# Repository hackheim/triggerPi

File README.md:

# triggerPi
DSLR Remote trigger kippah  for Raspberry Pi

<br />This work is licensed under a <a rel="license" href="http://creativecommons.org/licenses/by-sa/4.0/">Creative Commons Attribution-ShareAlike 4.0 International License</a>.

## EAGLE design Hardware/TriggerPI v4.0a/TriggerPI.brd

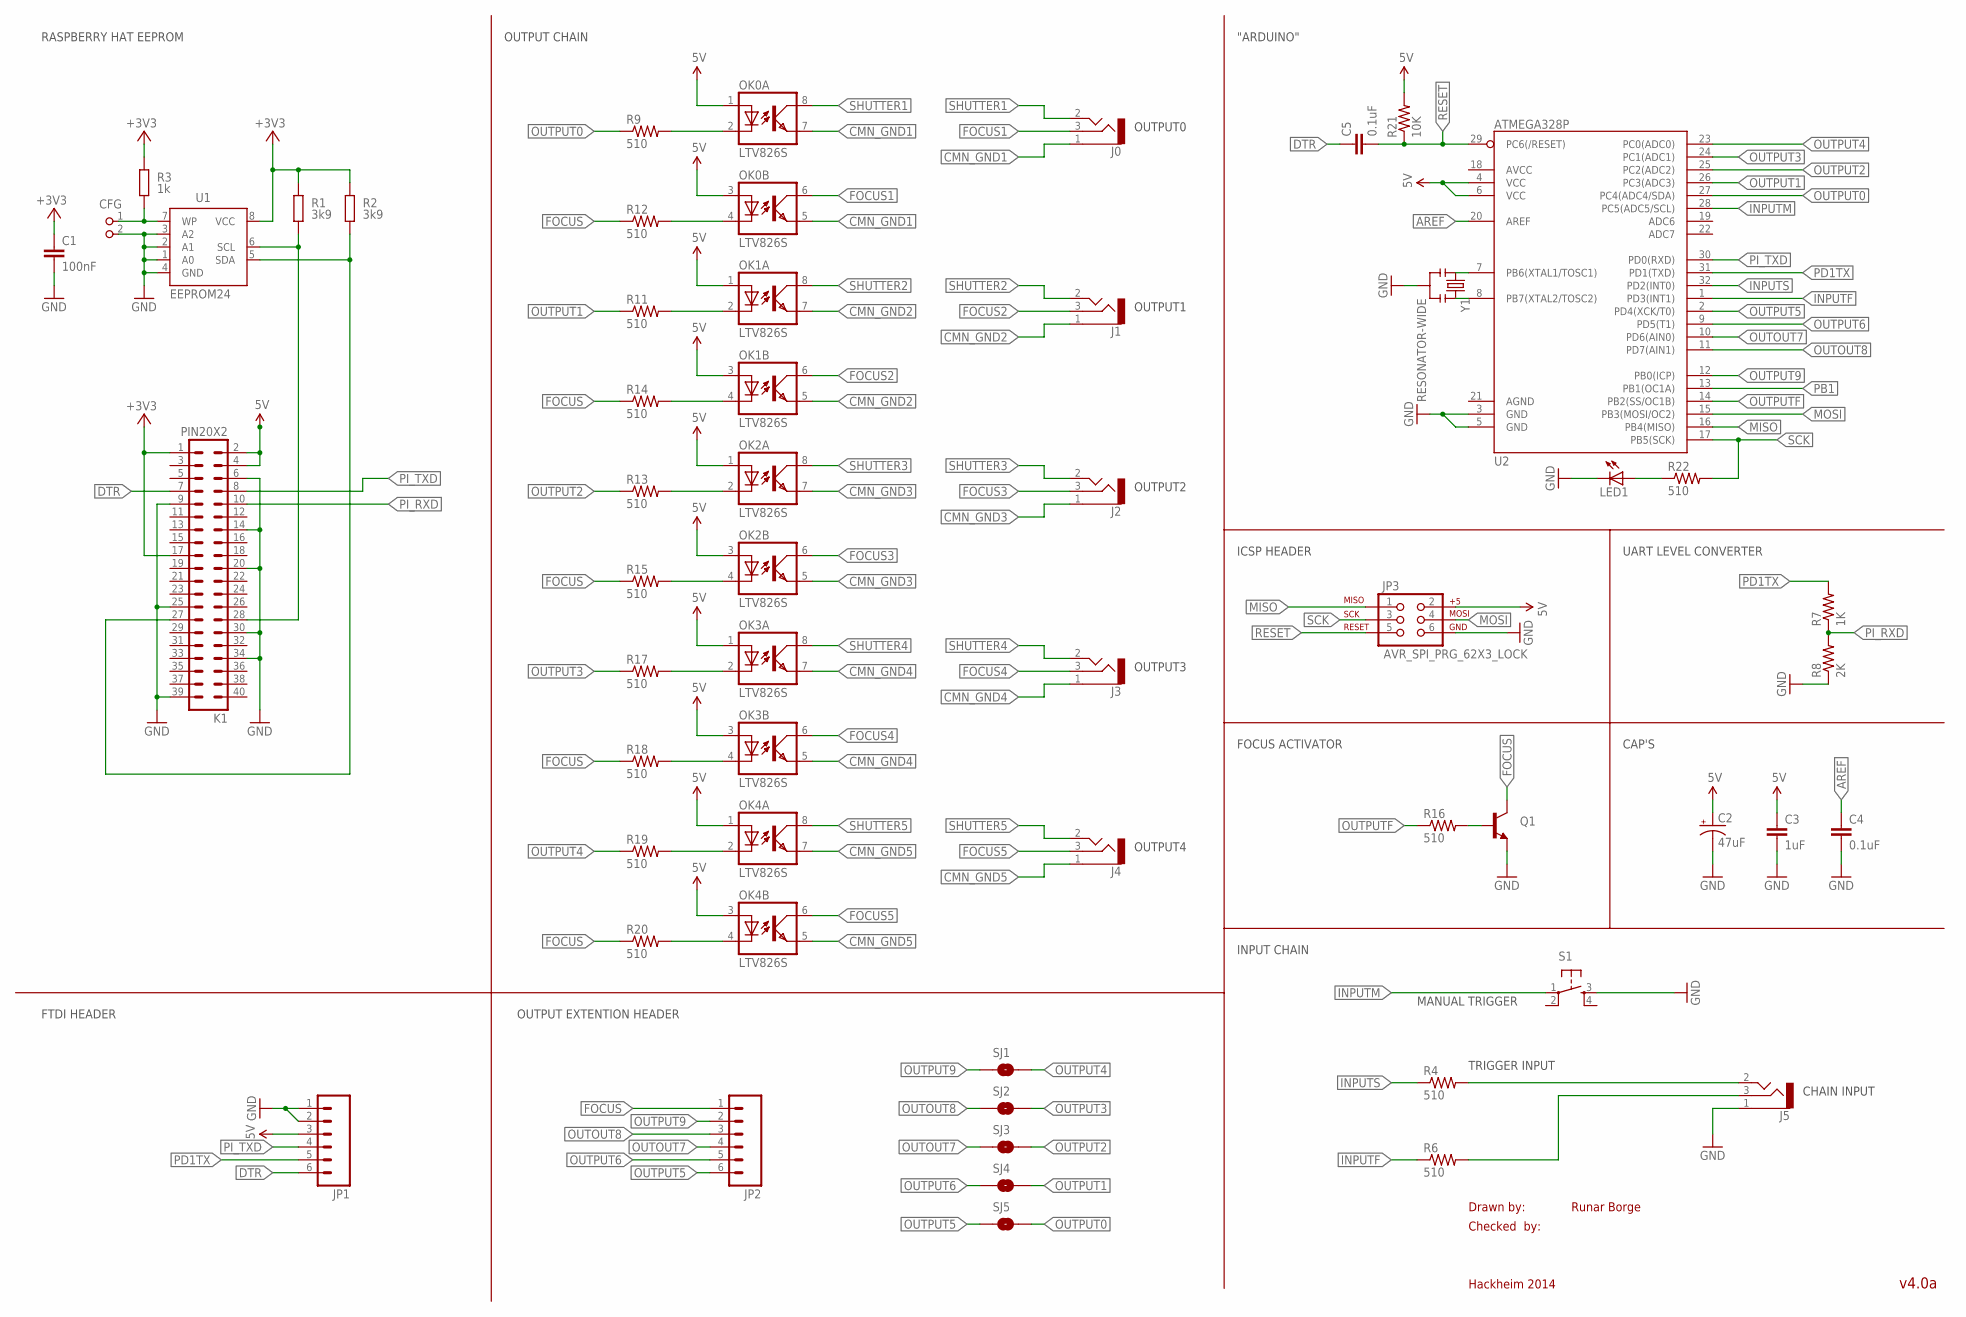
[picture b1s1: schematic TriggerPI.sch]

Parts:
C1: 100nF; C0805K
C2: 47uF; EIA3528; DIGIKEY 478-3132-1-ND
C3: 1uF; 0805; DIGIKEY 445-7547-1-ND
C4, C5: 0.1uF; 0603-CAP; DIGIKEY 445-1314-1-ND
CFG: PIN2_100; PIN_W_2
J0, J1, J2, J3, J4, J5: AUDIO-3P'SJ-3523-SMT'; 3P-SMD-3.5; DIGIKEY CP-3523SJCT-ND
JP1, JP2: M06LOCK; 1X06_LOCK
JP3: AVR_SPI_PRG_62X3_LOCK; 2X3_LOCK
K1: PIN20X2; PIN_20X2
LED1: LED1206; LED-1206; DIGIKEY 160-1405-1-ND
OK0, OK1, OK2, OK3, OK4: LTV826S; DIL8-SMD; DIGIKEY 160-1363-5-ND
Q1: TRANSISTOR_NPNSOT23-3; SOT23-3; DIGIKEY MMBT2222A-FDICT-ND
R1, R2: 3k9; M0805; TOLERANCE 5%
R3: 1k; M0805; TOLERANCE 5%
R4, R6, R9, R11, R12, R13, R14, R15, R16, R17, R18, R19, R20, R22: 510; 0603-RES; DIGIKEY RMCF0603JT510RCT-ND
R7: 1K; 0603-RES; DIGIKEY RMCF0603JT1K00CT-ND
R8: 2K; 0603-RES; DIGIKEY RMCF0603JT2K00CT-ND
R21: 10K; 0603-RES; DIGIKEY RMCF0603JT10K0CT-ND
S1: TAC_SWITCHSMD; TACTILE_SWITCH_SMD; DIGIKEY CKN9104CT-ND
SJ1, SJ2, SJ3, SJ4, SJ5: JUMPER-PAD-2-NOYES_SILK; PAD-JUMPER-2-NO_YES_SILK
U1: EEPROM24; SOIC8
U2: ATMEGA328P; TQFP32-08; DIGIKEY ATMEGA328P-AURCT-ND
Y1: RESONATOR-WIDE; RESONATOR-WIDE-SMD; DIGIKEY 1253-1084-1-ND

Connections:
5V: C2.A (+), C3.1, JP1.3, JP3.2, K1.2, K1.4, OK0.1 (A), OK0.3 (A), OK1.1 (A), OK1.3 (A), OK2.1 (A), OK2.3 (A), OK3.1 (A), OK3.3 (A), OK4.1 (A), OK4.3 (A), R21.2, U2.4 (VCC), U2.6 (VCC)
+3V3: C1.1, K1.1, K1.17, R1.2, R2.2, R3.2, U1.8 (VCC)
AREF: C4.1, U2.20 (AREF)
CMN_GND1: J0.1, OK0.5 (EMIT), OK0.7 (EMIT)
CMN_GND2: J1.1, OK1.5 (EMIT), OK1.7 (EMIT)
CMN_GND3: J2.1, OK2.5 (EMIT), OK2.7 (EMIT)
CMN_GND4: J3.1, OK3.5 (EMIT), OK3.7 (EMIT)
CMN_GND5: J4.1, OK4.5 (EMIT), OK4.7 (EMIT)
DTR: C5.1, JP1.6, K1.7
FOCUS: JP2.1, Q1.3 (C), R12.1, R14.1, R15.1, R18.1, R20.1
FOCUS0: J5.3 (2), R6.2
FOCUS1: J0.3 (2), OK0.6 (COL)
FOCUS2: J1.3 (2), OK1.6 (COL)
FOCUS3: J2.3 (2), OK2.6 (COL)
FOCUS4: J3.3 (2), OK3.6 (COL)
FOCUS5: J4.3 (2), OK4.6 (COL)
GND: C1.2, C2.C (-), C3.2, C4.2, CFG.2, J5.1, JP1.1, JP1.2, JP3.6, K1.6, K1.9, K1.14, K1.20, K1.25, K1.30, K1.34, K1.39, LED1.C, Q1.2 (E), R8.1, S1.3, U1.1 (A0), U1.2 (A1), U1.3 (A2), U1.4 (GND), U2.3 (GND), U2.5 (GND), Y1.2
INPUTF: R6.1, U2.1 (PD3(INT1))
INPUTM: S1.1, U2.28 (PC5(ADC5/SCL))
INPUTS: R4.1, U2.32 (PD2(INT0))
MISO: JP3.1, U2.16 (PB4(MISO))
MOSI: JP3.4, U2.15 (PB3(MOSI/OC2))
unnamed: K1.28, R1.1, U1.6 (SCL)
unnamed: K1.27, R2.1, U1.5 (SDA)
unnamed: CFG.1, R3.1, U1.7 (WP)
unnamed: J5.2 (5), R4.2
unnamed: OK0.2 (C), R9.2
unnamed: OK1.2 (C), R11.2
unnamed: OK2.2 (C), R13.2
unnamed: OK0.4 (C), R12.2
unnamed: Q1.1 (B), R16.2
unnamed: OK3.2 (C), R17.2
unnamed: OK3.4 (C), R18.2
unnamed: OK4.2 (C), R19.2
unnamed: OK4.4 (C), R20.2
unnamed: U2.7 (PB6(XTAL1/TOSC1)), Y1.1
unnamed: U2.8 (PB7(XTAL2/TOSC2)), Y1.3
unnamed: LED1.A, R22.1
unnamed: OK1.4 (C), R14.2
unnamed: OK2.4 (C), R15.2
OUTOUT7: JP2.4, SJ3.1, U2.10 (PD6(AIN0))
OUTOUT8: JP2.3, SJ2.1, U2.11 (PD7(AIN1))
OUTPUT0: R9.1, SJ5.2, U2.27 (PC4(ADC4/SDA))
OUTPUT1: R11.1, SJ4.2, U2.26 (PC3(ADC3))
OUTPUT2: R13.1, SJ3.2, U2.25 (PC2(ADC2))
OUTPUT3: R17.1, SJ2.2, U2.24 (PC1(ADC1))
OUTPUT4: R19.1, SJ1.2, U2.23 (PC0(ADC0))
OUTPUT5: JP2.6, SJ5.1, U2.2 (PD4(XCK/T0))
OUTPUT6: JP2.5, SJ4.1, U2.9 (PD5(T1))
OUTPUT9: JP2.2, SJ1.1, U2.12 (PB0(ICP))
OUTPUTF: R16.1, U2.14 (PB2(SS/OC1B))
PB1: U2.13 (PB1(OC1A))
PD1TX: JP1.5, R7.2, U2.31 (PD1(TXD))
PI_RXD: K1.10, R7.1, R8.2
PI_TXD: JP1.4, K1.8, U2.30 (PD0(RXD))
RESET: C5.2, JP3.5, R21.1, U2.29 (PC6(/RESET))
SCK: JP3.3, R22.2, U2.17 (PB5(SCK))
SHUTTER1: J0.2 (5), OK0.8 (COL)
SHUTTER2: J1.2 (5), OK1.8 (COL)
SHUTTER3: J2.2 (5), OK2.8 (COL)
SHUTTER4: J3.2 (5), OK3.8 (COL)
SHUTTER5: J4.2 (5), OK4.8 (COL)

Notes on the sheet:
Drawn by:
Checked by:
Hackheim 2014
Runar Borge
v4.0a
CHAIN INPUT
OUTPUT0
OUTPUT1
OUTPUT2
OUTPUT3
OUTPUT4
MANUAL TRIGGER
INPUT CHAIN
OUTPUT CHAIN
ICSP HEADER
FTDI HEADER
FOCUS ACTIVATOR
UART LEVEL CONVERTER
"ARDUINO"
TRIGGER INPUT
CAP'S
RASPBERRY HAT EEPROM
OUTPUT EXTENTION HEADER

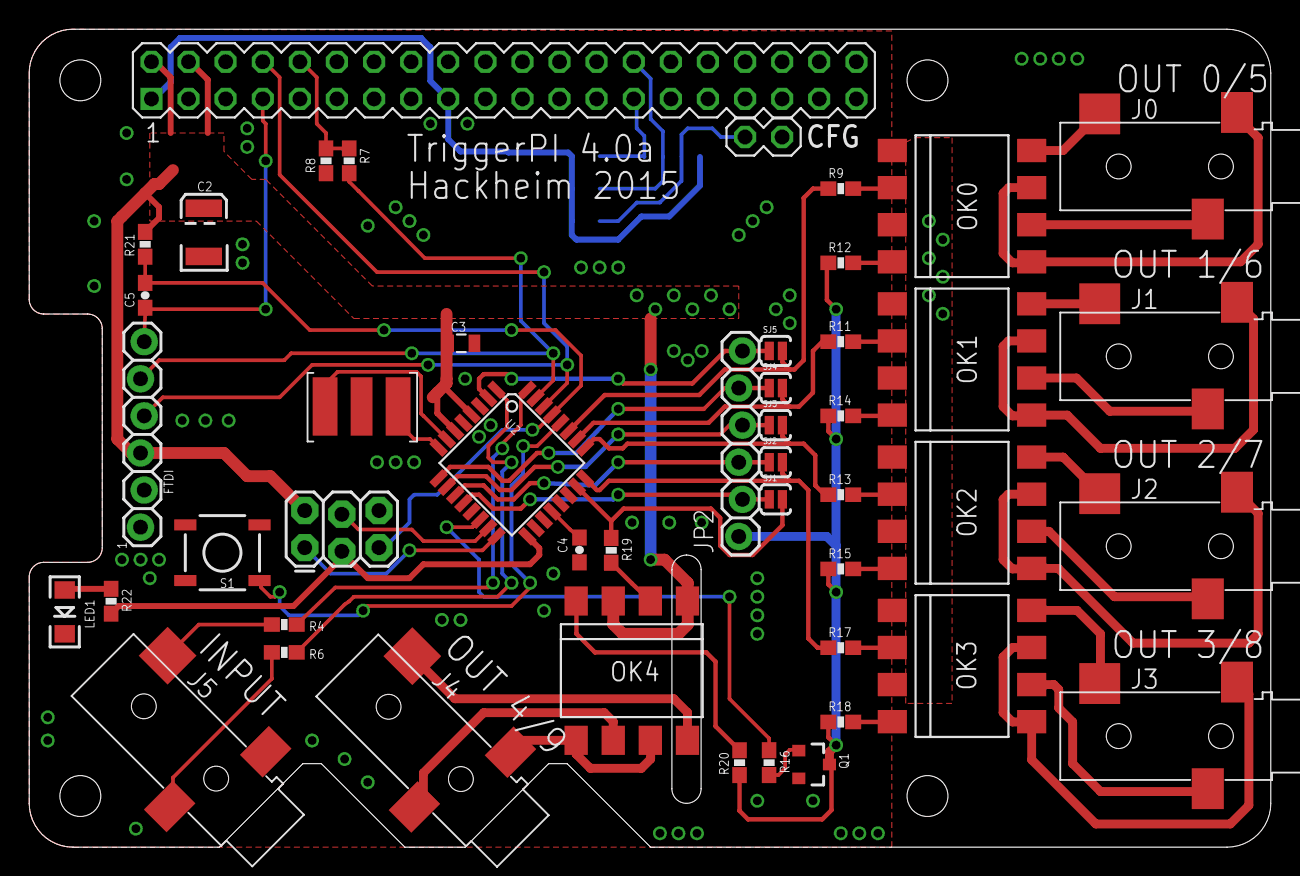
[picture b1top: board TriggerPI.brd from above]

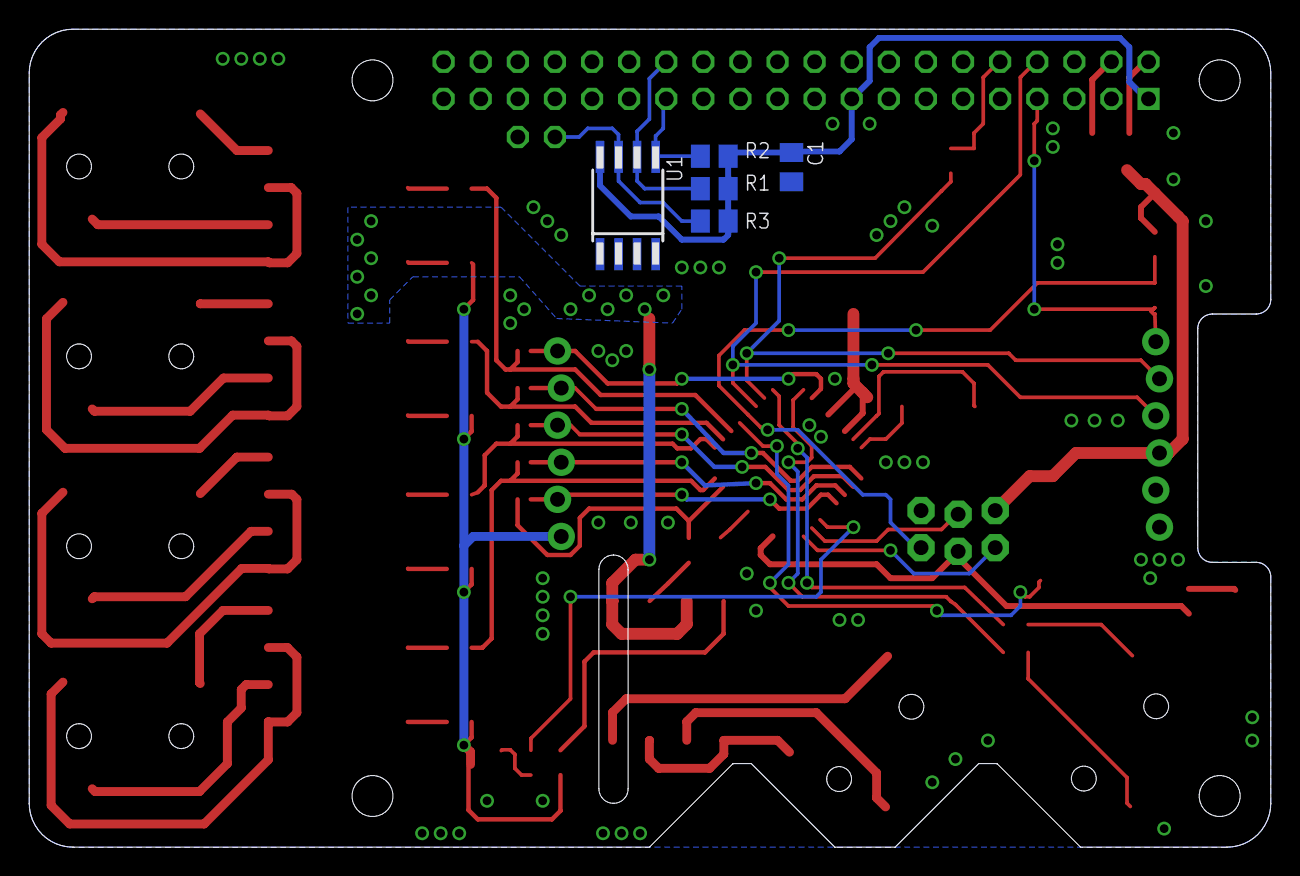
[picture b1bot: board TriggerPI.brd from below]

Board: 2 copper layers, 85.0 x 56.0 mm, 52 parts (5 on the bottom side), 61 nets.

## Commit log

2015-09-20 Uploaded License
    Creative Commons BY SA 4
2015-09-20 Uploaded version 4.0a
2015-09-20 Uploaded board in pdf format

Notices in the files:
parts and their libraries:
SparkFun-Passives: Licensing: CC v3.0 Share-Alike You are welcome to use this library for commercial purposes.
